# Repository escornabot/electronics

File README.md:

## Catalog
- [Escorna CPU][CPU01] is 50x50mm to 50x100mm board to use with Arduino Nano. It integrates keypad on board on 2x

- [Escorna_CPU_2_4][CPU240] It is a pcb that integrates an ATmega328P, a step-up (to use 1.2V batteries) and the rest of the electronics needed to build an Escornabot.

- [Arduino Shield][ARD01] is an Arduino Uno compatible
  shield ready to use with the Escornabot's motors and also integrates a keypad.

- [Cervus][CER01] is a board based on powerful ATmega32u4
  microcontroler and compatible with Arduino shields.
- [E_Keypad][KEY01] Is a 50x50mm board with 6  and 5 buttons and
  connects to any Escornabot.

- [E_KEY_BT][E_KEY_BT] Escornabot keyboard with MakeyMakey type sensors on the E_KEY_BT board.
   Any object that is minimally conductive can be used. Adjusting the value
   threshold: higher for less sensitivity, nothing needs to be changed in the
   robot firmware.

- [E_KEY_FICHA][E_KEY_FICHA] It allows the programming of Escornabot using printed or cut-out cards (cardboard ..) communicating the commands via Bluetooth.
  using @arduino Nano, easy to print, manageable and expandable to 15 "Tabs" thanks to the firmware of @caligari_pub

- [escoRnaFID][RnaFID]PCB for the project for children with visual impairment or blindness,
  developed by Angel Villanueva [@avilmaru][@avil] to control an Escornabot with RFID cards

## License

Every content in this repo, otherwise specified under subdirectories, is
licensed under [Creative Commons BY-SA][LICENSEcc] or [CERN Open Hardware Licence -W- V2][OHL-W-V2].
(by [XDeSIG][XDE01])

## To buy boards

Developer don't produce boards to sell. Under [_provider_][provider]
directory there are instructions to order yourself.

Are you a board provider? Please, send us your buyer's guide! :-)

[CPU01]: EscornaCPU
[CPU240]: https://github.com/xdesig/escornabot-electronics/tree/master/Electronics/EscornaCPU/2.x/2.40
[ARD01]: ArduinoShield
[CER01]: Cervus
[KEY01]: E_KEYPAD
[RnaFID]: escoRnaFID
[E_KEY_BT]: E_KEY_BT
[@avil]: https://twitter.com/avilmaru
[XDE01]: https://twitter.com/xdesig
[provider]: https://www.pcbway.com/project/member/?bmbno=6FE4DE76-9D11-4C
[LICENSEcc]: https://creativecommons.org/licenses/by-sa/3.0/es
[OHL-W-V2]: https://ohwr.org/project/cernohl/wikis/Documents/CERN-OHL-version-2

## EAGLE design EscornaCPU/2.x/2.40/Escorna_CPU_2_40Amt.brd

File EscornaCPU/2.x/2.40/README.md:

## Escorna CPU 2.4
This PCB integrates an ATmega328P, a step-up (great to use with 1.2V batteries, suggestion made by [caligari](https://github.com/rafacouto)) and the rest of the electronics needed to build a full-compatible Escornabot.
USB communications are supported by CH340E<br>
Arduino Uno, Arduino Nano compatible or ATmega minicore

## License

<br><br><br><br>

## Open Hardware Certification program

<br><br><br><br><br><br><br>

## To buy boards
Developer doesn't produce boards to get money. [_provider_][provider]

Are you a board provider? Please, send us your buyer's guide! xdesig@gmail.com

[XDE01]: https://twitter.com/xdesig
[provider]: https://www.pcbway.com/project/shareproject/Escorna_CPU_2_4.html
[LICENSEcc]: https://creativecommons.org/licenses/by-sa/3.0/es
[OHL-W-V2]: https://ohwr.org/project/cernohl/wikis/Documents/CERN-OHL-version-2

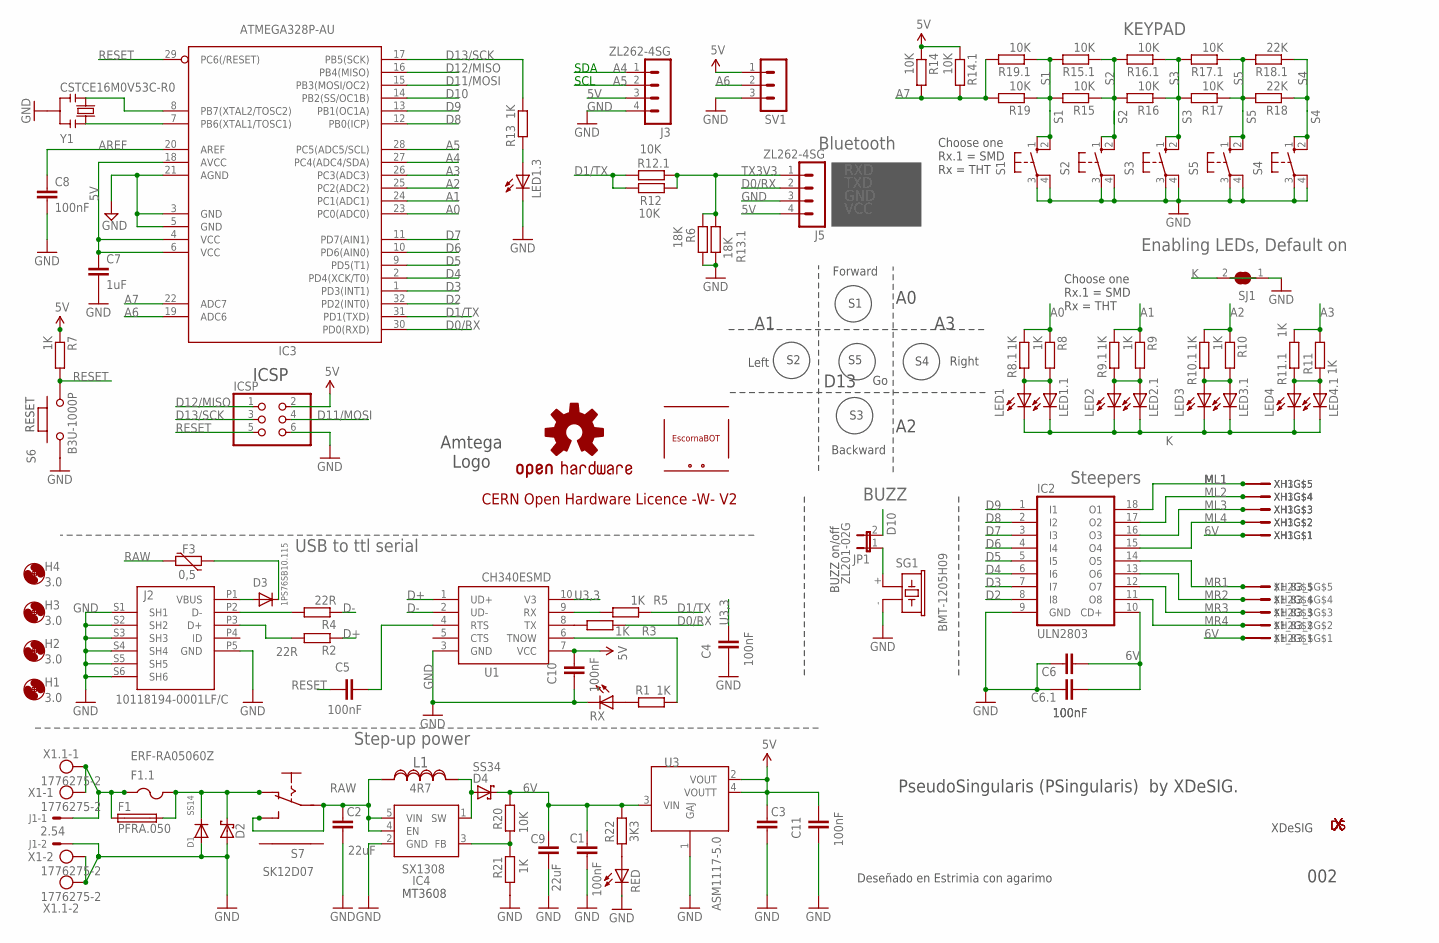
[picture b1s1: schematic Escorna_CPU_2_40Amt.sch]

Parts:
$1_82_$: XDESIG_XDESIG21; XDESIG_XDESIG
$1_83_$: B5B-XH-A
C1, C4, C5, C8, C10, C11: 100nF; C0603-ROUND
C2, C9: 22uF; C1206K
C3: 10uF; C1206K
C6: 100nF; C025-024X044
C6.1: 100nF; C0603K
C7: 1uF; C0603-ROUND
D1: SS14; SMADIODE
D2: 1N5817; DO41-10
D3: 1PS76SB10.115; SOD-323F
D4: SS34; DIODE_SMA
ESC: ESCORNABOT; ESCORNA_PEQUE
F1: PFRA.050; TE5
F1.1: ERF-RA05060Z; R1206
F3: 0,5; R1206
H1, H2, H3, H4: 3.0; 3,0
IC2: ULN2803; DIL18
IC3: ATMEGA328P-AU; TQFP32-08
IC4: SX1308; SOT23-6
ICSP: 0114_PH254-203DF118A00V; 2X03
J1: 2.54; 6410-02
J2: 10118194-0001LF/C; SMARTPRJ_CON2_USB_MICRO_B_AT
J3, J5: ZL262-4SG; MA04-1
JP1: ZL201-02G; JP1
L1: 4R7; SRN6045
LED1, LED2, LED3, LED4: LED3MM
LED1.1, LED1.3, LED2.1, LED3.1, LED4.1: LEDCHIPLED_0603; CHIPLED_0603
LOGO2: OSHW-LOGOL; ESCORNA_LBRESCORNA_CPU_2_10_SPARKFUN-AESTHETICS_OSHW-LOGO-L
R1, R3, R5, R7, R8.1, R9.1, R10.1, R11.1, R13, R21: 1K; R0603
R2, R4: 22R; R0603
R6: 18K; 0204/7
R8, R9, R10, R11: 1K; 0204/7
R12, R14, R15, R16, R17, R19: 10K; 0204/7
R12.1, R14.1, R15.1, R16.1, R17.1, R19.1, R20: 10K; R0603
R13.1: 18K; R0603
R18: 22K; 0204/7
R18.1: 22K; R0603
R22: 3K3; R0603
RED: LEDCHIPLED_0603; CHIPLED_0603
RX: LEDCHIPLED_0603; CHIPLED_0603
S1, S2, S3, S4, S5: 40-XX; B3F-40
S6: B3U-1000P; SMD_157SW
S7: SK12D07; ESCORNA_SK-12D07
SG1: BMT-1205H09; F/CM12P
SJ1: SJ
SV1: MA03-1
U1: CH340ESMD; MSOP10
U3: ASM1117-5.0; SOT223
X1, X1.1: 1776275-2; AK550/2
XDS2: XDESIG; XDESIG_CU_2
XH1, XH2, XH3: B5B-XH-A
Y1: CSTCE16M0V53C-R0; RESONATOR

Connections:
5V: C3.2, C7.1, C10.2, C11.2, IC3.4 (VCC), IC3.6 (VCC), IC3.18 (AVCC), ICSP.2, J3.3, J5.4, R7.1, R14.1, R14.1.1, SV1.1, U1.7 (VCC), U3.2 (VOUT), U3.4 (VOUTT)
6V: $1_83_$.P$1, C1.2, C6.2, C6.1.2, C9.2, D4.C, IC2.10 (CD+), R20.1, R22.1, U3.3 (VIN), XH1.P$1, XH2.P$1, XH3.P$1
+D: J2.P3 (D+), R2.2
-D: J2.P2 (D-), R4.2
A0: IC3.23 (PC0(ADC0)), R8.1, R8.1.1
A1: IC3.24 (PC1(ADC1)), R9.1, R9.1.1
A2: IC3.25 (PC2(ADC2)), R10.1, R10.1.1
A3: IC3.26 (PC3(ADC3)), R11.2, R11.1.1
A4: IC3.27 (PC4(ADC4/SDA)), J3.1
A5: IC3.28 (PC5(ADC5/SCL)), J3.2
A6: IC3.19 (ADC6), SV1.2
A7: IC3.22 (ADC7), R14.2, R14.1.2, R19.2, R19.1.2
AREF: C8.1, IC3.20 (AREF)
D0/RX: IC3.30 (PD0(RXD)), J5.2, R3.1
D1/TX: IC3.31 (PD1(TXD)), R5.1, R12.1, R12.1.1
D2: IC2.8 (I8), IC3.32 (PD2(INT0))
D3: IC2.7 (I7), IC3.1 (PD3(INT1))
D4: IC2.6 (I6), IC3.2 (PD4(XCK/T0))
D5: IC2.5 (I5), IC3.9 (PD5(T1))
D6: IC2.4 (I4), IC3.10 (PD6(AIN0))
D7: IC2.3 (I3), IC3.11 (PD7(AIN1))
D8: IC2.2 (I2), IC3.12 (PB0(ICP))
D9: IC2.1 (I1), IC3.13 (PB1(OC1A))
D10: IC3.14 (PB2(SS/OC1B)), JP1.2
D11/MOSI: IC3.15 (PB3(MOSI/OC2)), ICSP.4
D12/MISO: IC3.16 (PB4(MISO)), ICSP.1
D13/SCK: IC3.17 (PB5(SCK)), ICSP.3, R13.1
D+: R2.1, U1.1 (UD+)
D-: R4.1, U1.2 (UD-)
DTR?: C5.2, U1.4 (RTS)
GND: C1.1, C2.1, C3.1, C4.1, C6.1, C6.1.1, C7.2, C8.2, C9.1, C10.1, C11.1, D1.A, D2.A, IC2.9 (GND), IC3.3 (GND), IC3.5 (GND), IC3.21 (AGND), IC4.2 (GND), ICSP.6, J1.2, J2.P5 (GND), J2.S1 (SH1), J2.S2 (SH2), J2.S3 (SH3), J2.S4 (SH4), J2.S5 (SH5), J2.S6 (SH6), J3.4, J5.3, LED1.3.C, R6.2, R13.1.1, R21.2, RED.C, RX.C, S1.3, S1.4 (P1), S2.3, S2.4 (P1), S3.3, S3.4 (P1), S4.3, S4.4 (P1), S5.3, S5.4 (P1), S6.1, SG1.- (2), SJ1.1, SV1.3, U1.3 (GND), U3.1 (GAJ), X1.2, X1.1.2, Y1.2
K: LED1.K (C), LED1.1.C, LED2.K (C), LED2.1.C, LED3.K (C), LED3.1.C, LED4.K (C), LED4.1.C, SJ1.2
ML1: IC2.18 (O1), XH1.P$5, XH3.P$5
ML2: IC2.17 (O2), XH1.P$4, XH3.P$4
ML3: IC2.16 (O3), XH1.P$3, XH3.P$3
ML4: IC2.15 (O4), XH1.P$2, XH3.P$2
MR1: $1_83_$.P$5, IC2.14 (O5), XH2.P$5
MR2: $1_83_$.P$4, IC2.13 (O6), XH2.P$4
MR3: $1_83_$.P$3, IC2.12 (O7), XH2.P$3
MR4: $1_83_$.P$2, IC2.11 (O8), XH2.P$2
unnamed: JP1.1, SG1.+ (1)
unnamed: D1.C, D2.C, F1.2, F1.1.2, S7.P$2 (O)
unnamed: LED2.A, LED2.1.A, R9.2, R9.1.2
unnamed: LED1.A, LED1.1.A, R8.2, R8.1.2
unnamed: LED3.A, LED3.1.A, R10.2, R10.1.2
unnamed: LED4.A, LED4.1.A, R11.1, R11.1.2
unnamed: D3.A, J2.P1 (VBUS)
unnamed: F1.1, F1.1.1, J1.1, X1.1, X1.1.1
unnamed: R1.2, RX.A
unnamed: IC4.3 (FB), R20.2, R21.1
unnamed: IC3.7 (PB6(XTAL1/TOSC1)), Y1.1
unnamed: IC3.8 (PB7(XTAL2/TOSC2)), Y1.3
unnamed: LED1.3.A, R13.2
unnamed: D4.A, IC4.1 (SW), L1.1
unnamed: D3.C, F3.1
unnamed: R22.2, RED.A
unnamed: R5.2, U1.9 (RX)
unnamed: R3.2, U1.8 (TX)
unnamed: R1.1, U1.6 (TNOW)
RAW: C2.2, F3.2, IC4.4 (EN), IC4.5 (VIN), L1.2, S7.P$1, S7.P$3 (S)
RESET: C5.1, IC3.29 (PC6(/RESET)), ICSP.5, R7.2, S6.2
S1: R15.2, R15.1.2, R19.1, R19.1.1, S1.1 (S), S1.2 (S1)
S2: R15.1, R15.1.1, R16.2, R16.1.2, S2.1 (S), S2.2 (S1)
S3: R16.1, R16.1.1, R17.2, R17.1.2, S3.1 (S), S3.2 (S1)
S4: R18.1, R18.1.1, S4.1 (S), S4.2 (S1)
S5: R17.1, R17.1.1, R18.2, R18.1.2, S5.1 (S), S5.2 (S1)
TX3V3: J5.1, R6.1, R12.2, R12.1.2, R13.1.2
U3,3: C4.2, U1.10 (V3)

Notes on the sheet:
Steepers
KEYPAD
BUZZ
CERN Open Hardware Licence -W- V2
Forward
Left
Right
Backward
Choose one Rx.1 = SMD Rx = THT
XDeSIG
PseudoSingularis (PSingularis) by XDeSIG.
002
Enabling LEDs, Default on
BUZZ on/off
D13
SCL
SDA
ICSP
Bluetooth
RXD
TXD
GND
VCC
RESET
Deseñado en Estrimia con agarimo
SX1308
IC4
USB to ttl serial
Step-up power
MT3608
Amtega Logo

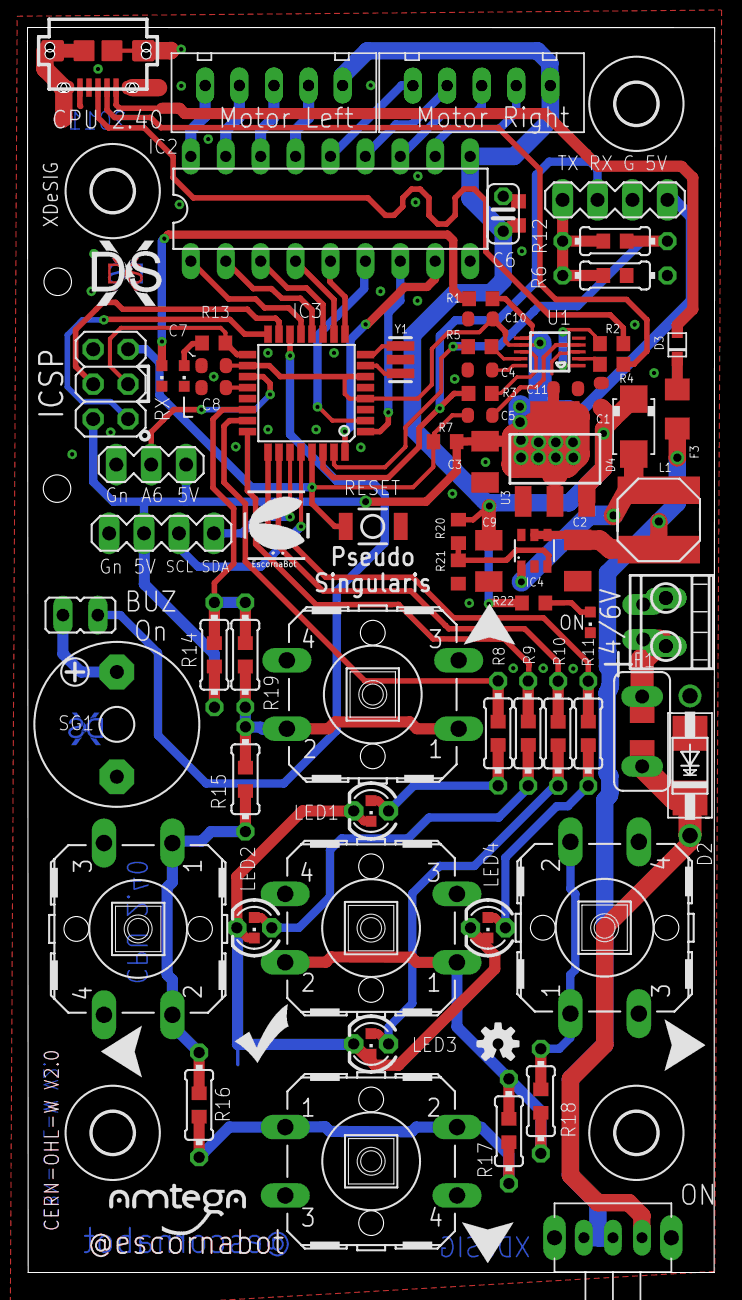
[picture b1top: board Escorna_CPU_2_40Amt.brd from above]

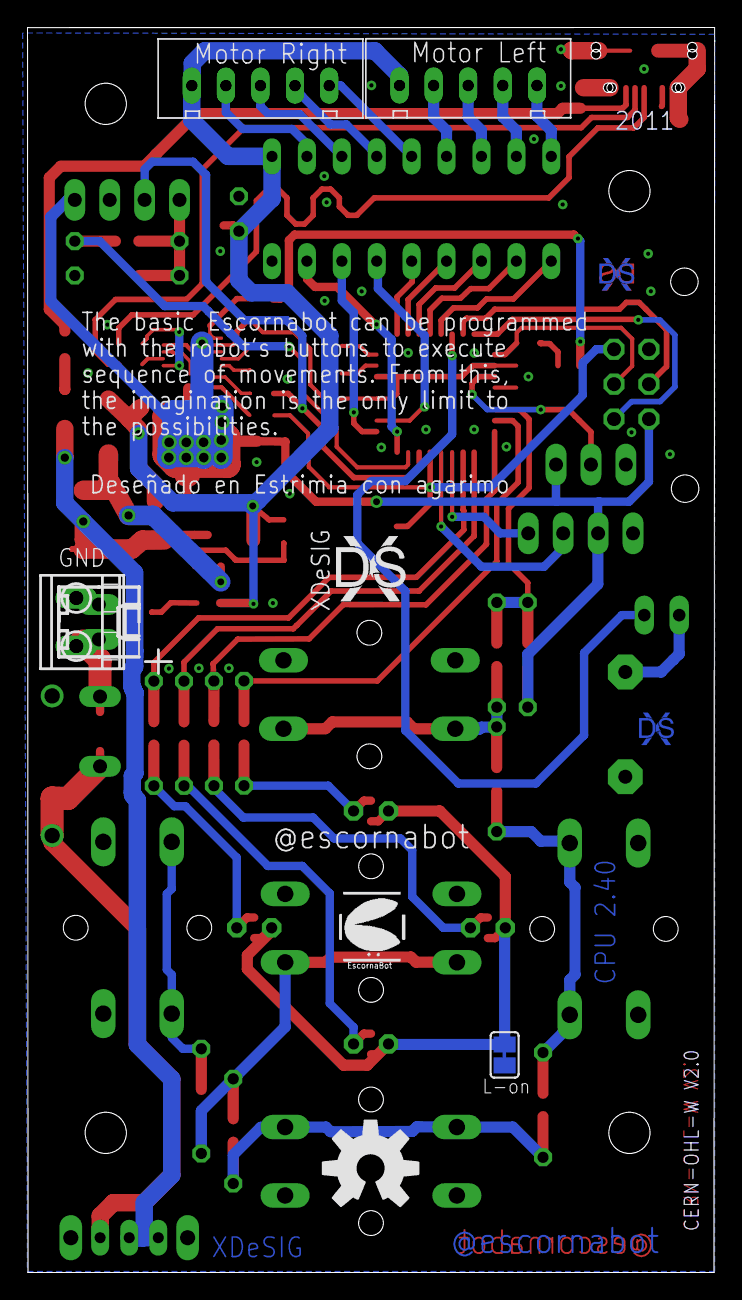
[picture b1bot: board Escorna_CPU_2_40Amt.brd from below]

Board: 2 copper layers, 50.0 x 90.6 mm, 112 parts (10 on the bottom side), 68 nets.

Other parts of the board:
LOGO1: OSHW-LOGOS; OSHW-LOGO-S
U$1: AMTEGA
U$4, U$7, U$8, U$9: FRECHA
U$5: ESCORNABOT; ESCORNA_PEQUE
U$10: GO; VALE
U$12: XDESIG_XDESIG21; XDESIG_XDESIG
XDS, XDS1: XDESIG; XDESIG_CU_2

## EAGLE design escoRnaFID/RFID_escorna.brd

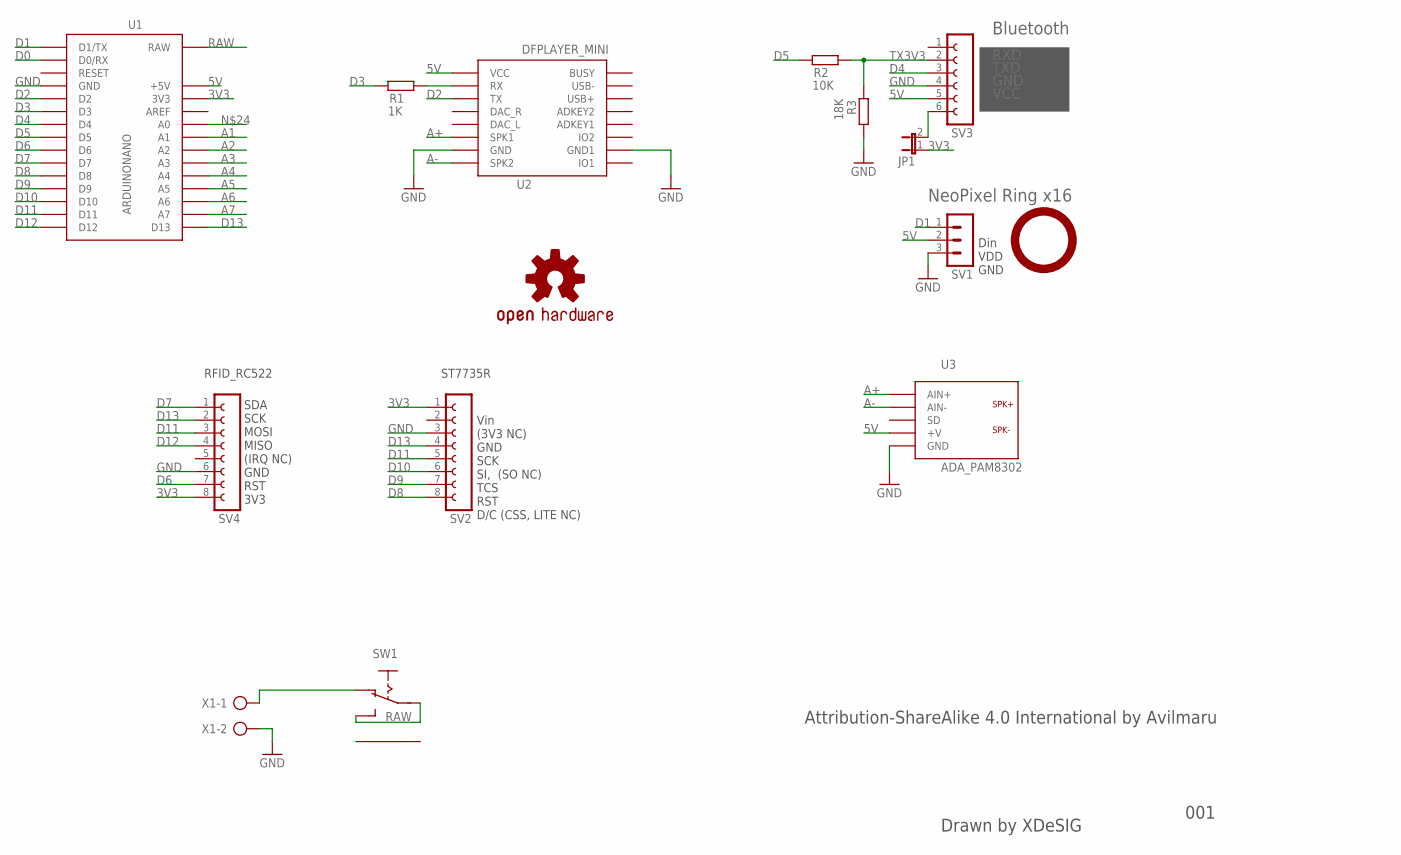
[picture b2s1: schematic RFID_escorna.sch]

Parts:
JP1: JUMPER_JP1E; JUMPER_JP1
LOGO1: OSHW-LOGOS; ESCORNA_LBRESCORNA_CPU_2_10_SPARKFUN-AESTHETICS_OSHW-LOGO-S
R1: 1K; 0204/7
R2: 10K; 0204/7
R3: 18K; 0204/7
SV1: MA03-1
SV2, SV4: FE08-1; FE08
SV3: FE06-1; FE06
SW1: ESCORNA_ELIB_ESCORNA_SK12F14D; ESCORNA_ELIB_ESCORNA_SK-12D07
U1: ARDUINONANO; ARDUINO_NANO_NO_ICSP
U2: DFPLAYER_MINI; DFR0299
U3: ADA_PAM8302; ADA_PAM8320
X1: AK500/2

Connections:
3V3: JP1.1, SV2.1, SV4.8, U1.3V3
5V: SV1.2, SV3.5, U1.5V (+5V), U2.P$1 (VCC), U3.P$2 (+V)
A1: U1.A1
A2: U1.A2
A3: U1.A3
A4: U1.A4
A5: U1.A5
A6: U1.A6
A7: U1.A7
A+: U2.P$6 (SPK1), U3.P$5 (AIN+)
A-: U2.P$8 (SPK2), U3.P$4 (AIN-)
D0: U1.D0/RX
D1: SV1.1, U1.D1/TX
D2: U1.D2, U2.P$3 (TX)
D3: R1.1, U1.D3
D4: SV3.3, U1.D4
D5: R2.1, U1.D5
D6: SV4.7, U1.D6
D7: SV4.1, U1.D7
D8: SV2.8, U1.D8
D9: SV2.7, U1.D9
D10: SV2.6, U1.D10
D11: SV2.5, SV4.3, U1.D11
D12: SV4.4, U1.D12
D13: SV2.4, SV4.2, U1.D13
GND: R3.2, SV1.3, SV2.3, SV3.4, SV4.6, U1.GND, U1.GND1 (GND), U2.P$7 (GND), U2.P$10 (GND1), U3.P$1 (GND), X1.2
unnamed: JP1.2, SV3.6
unnamed: SW1.P$2 (O), X1.1
unnamed: R1.2, U2.P$2 (RX)
RAW: SW1.P$1, SW1.P$3 (S), U1.RAW
TX3V3: R2.2, R3.1, SV3.2

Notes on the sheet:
Bluetooth
RXD
TXD
GND
VCC
NeoPixel Ring x16
RFID_RC522
SDA SCK MOSI MISO (IRQ NC) GND RST 3V3
ST7735R
Vin (3V3 NC) GND SCK SI, (SO NC) TCS RST D/C (CSS, LITE NC)
001
Din VDD GND
Attribution-ShareAlike 4.0 International by Avilmaru
Drawn by XDeSIG

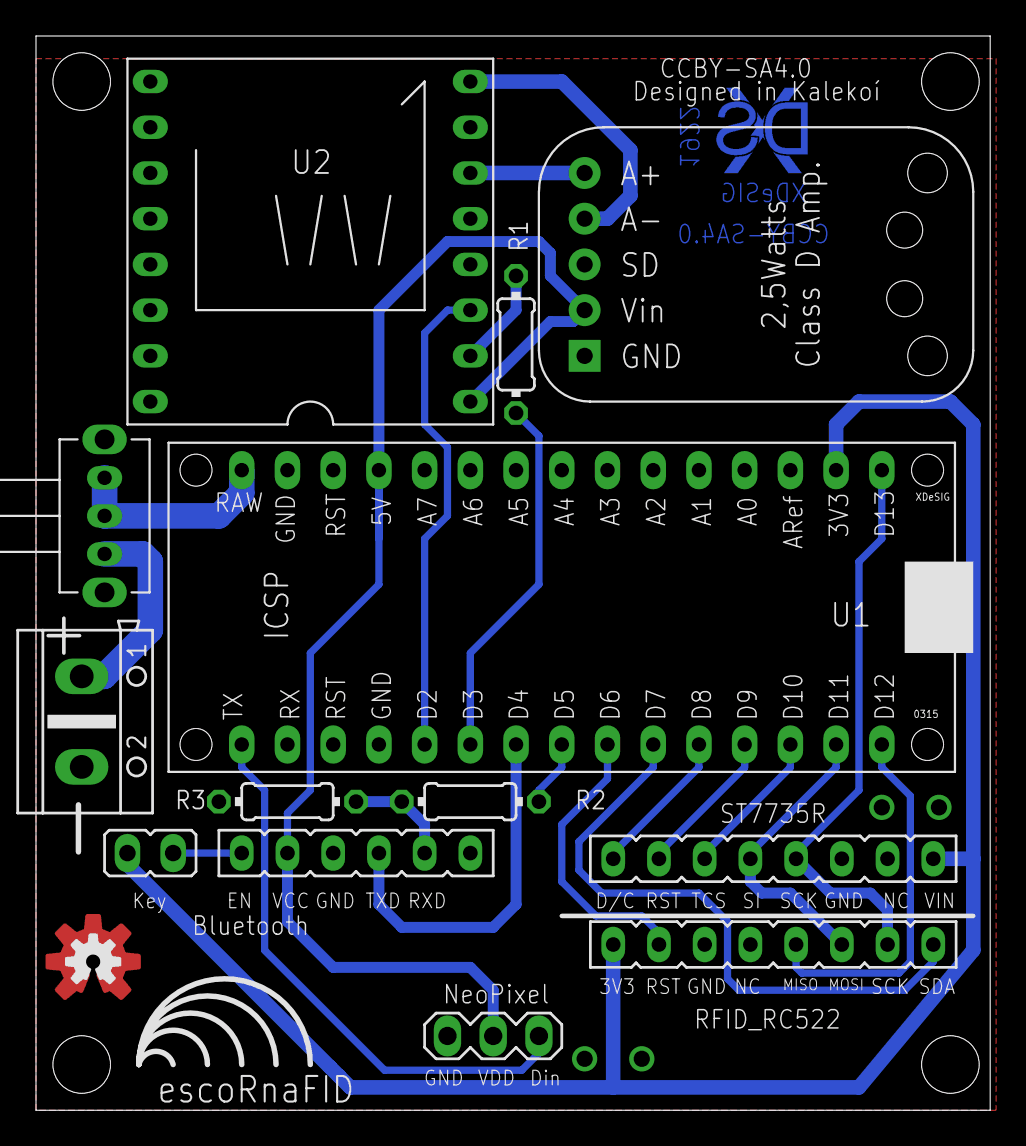
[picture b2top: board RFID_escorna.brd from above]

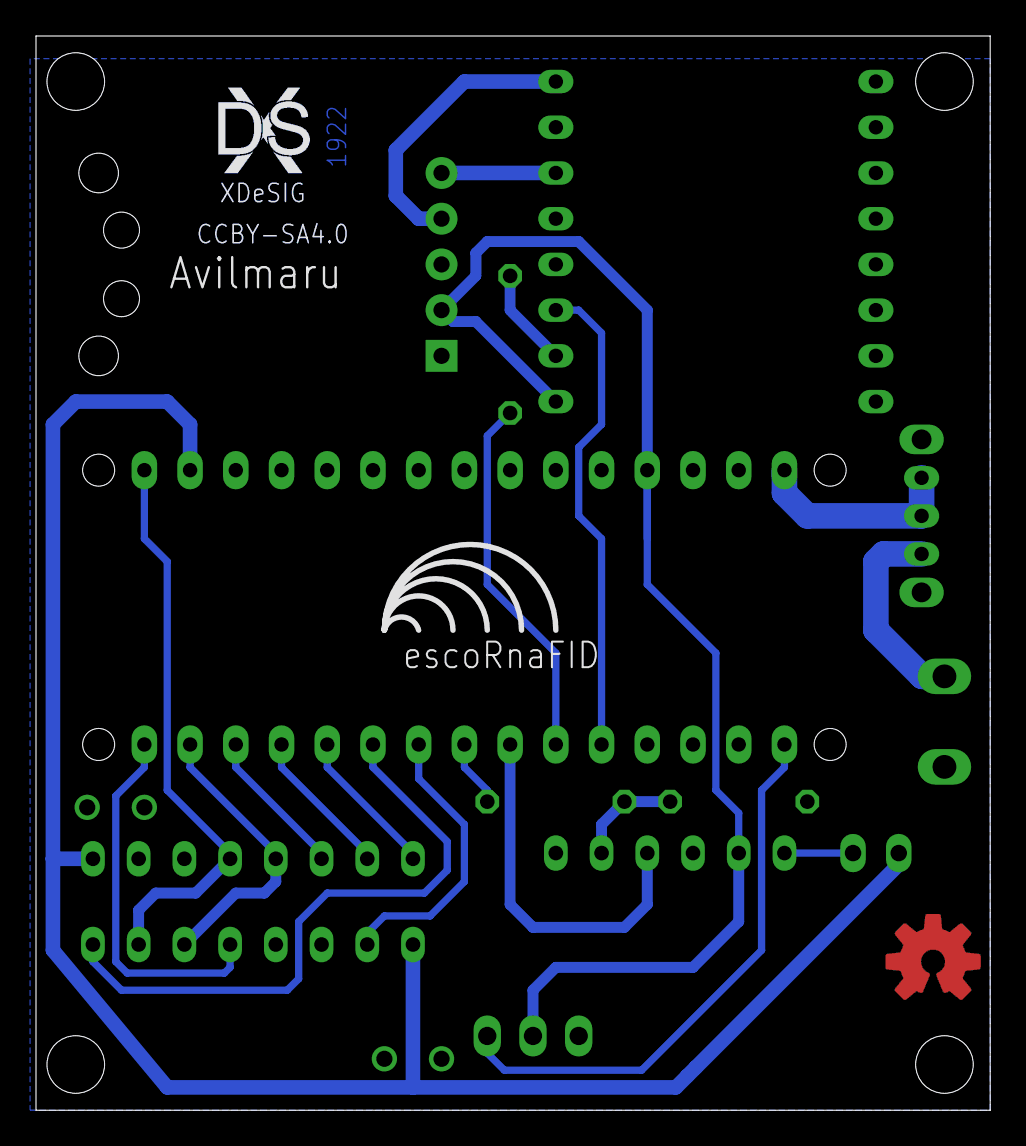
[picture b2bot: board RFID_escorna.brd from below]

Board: 2 copper layers, 53.0 x 59.7 mm, 17 parts (2 on the bottom side), 23 nets.

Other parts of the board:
U$1: XDESIG_CU
U$2: OSHWLOGO_TOP_0.2
U$5: XDESIG

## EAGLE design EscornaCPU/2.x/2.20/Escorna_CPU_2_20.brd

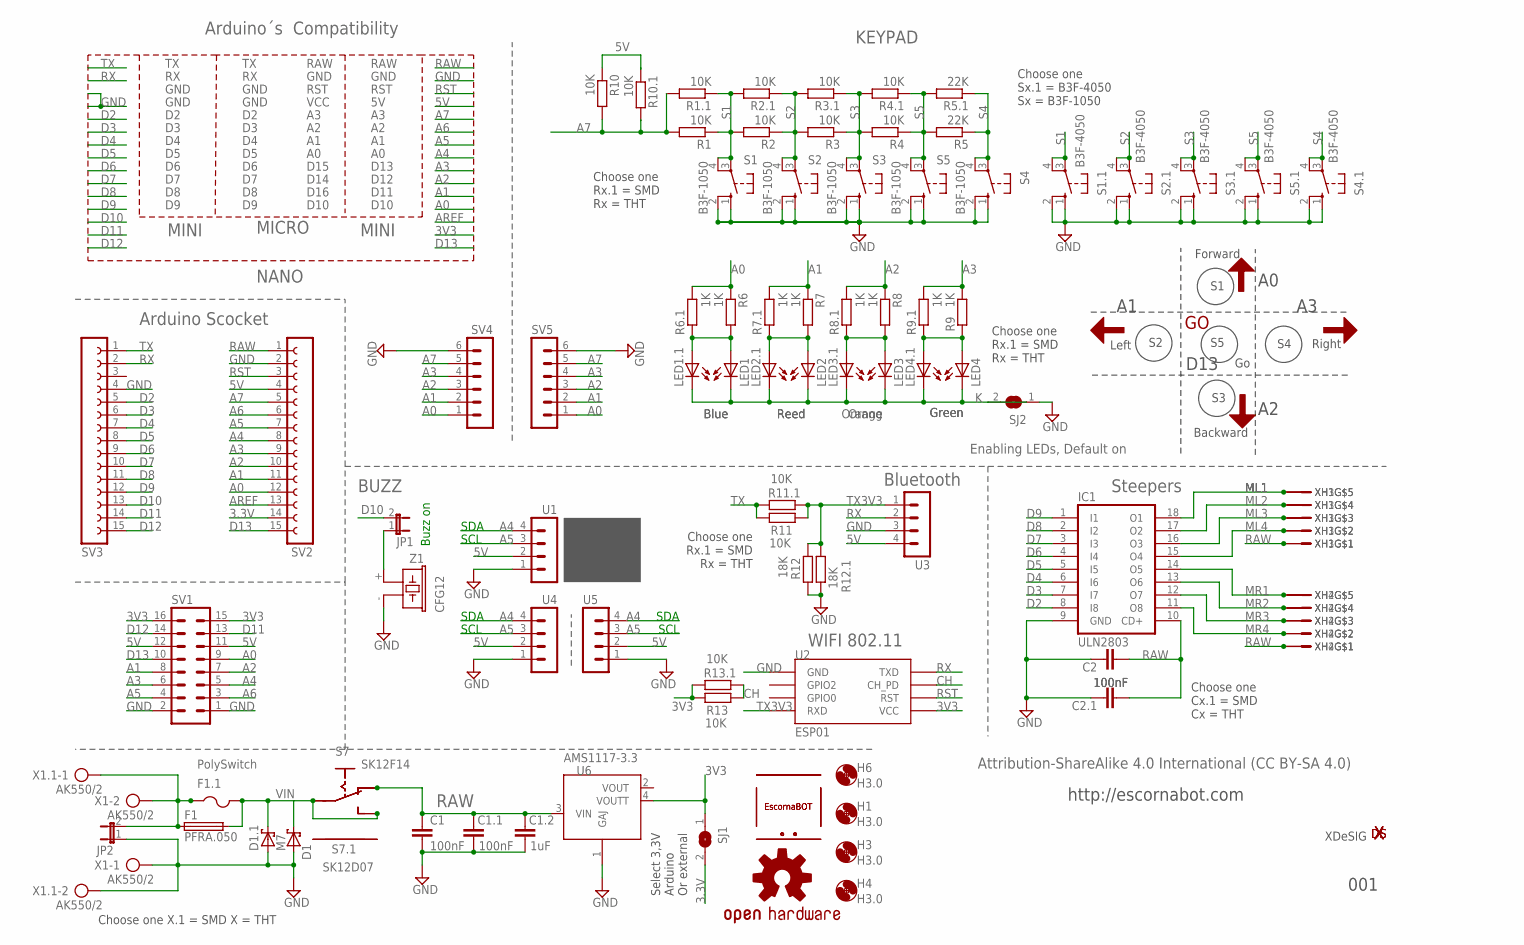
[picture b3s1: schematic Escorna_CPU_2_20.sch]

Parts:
C1, C2: 100nF; C025-025X050
C1.1, C2.1: 100nF; C0603K
C1.2: 1uF; C0603K
D1: 1N5817; DO41-10
D1.1: M7; SMA
ESC1, ESC2: ESCORNABOT; ESCORNA_PEQUE
F1: PFRA.050; TE5
F1.1: PolySwitch; R1206
H1, H3, H4, H6: H3.0; 3,0
IC1: ULN2803; DIL18
JP1, JP2: JP1E; 1X02
LED1: Blue; LED3MM
LED1.1: Blue; CHIPLED_0603
LED2: Reed; LED3MM
LED2.1: Reed; CHIPLED_0603
LED3: Orange; LED3MM
LED3.1: Orang; CHIPLED_0603
LED4: Green; LED3MM
LED4.1: Green; CHIPLED_0603
LOGO2: OSHW-LOGOS; OSHW-LOGO-S
R1, R2, R3, R4, R10, R11, R13: 10K; 0204/7
R1.1, R2.1, R3.1, R4.1, R10.1, R11.1, R13.1: 10K; R0603
R5: 22K; 0204/7
R5.1: 22K; R0603
R6, R7, R8, R9: 1K; 0204/7
R6.1, R7.1, R8.1, R9.1: 1K; R0603
R12: 18K; 0204/7
R12.1: 18K; R0603
S1, S2, S3, S4, S5: B3F-1050; B3F-10XX
S1.1, S2.1, S3.1, S4.1, S5.1: B3F-4050; B3F-40XX
S7: SK12F14; ESCORNA_SK-12F14-G
S7.1: SK12D07; ESCORNA_SK-12D07
SJ1, SJ2: SJ
SV1: MA08-2
SV2, SV3: 1x15 SOCKET STRIP; CON-LSTA_FE15
SV4, SV5: MA06-1
U1, U3, U4, U5: MA04-1
U2: ESP01
U6: AMS1117-3.3; SOT223
U$1, U$3, U$6, U$11: FRECHA
U$2: GO; VALE
U$13: XDESIG_XDESIG21; XDESIG_XDESIG
X1, X1.1: AK550/2
XDS1: XDESIG; XDESIG_CU_2
XH1, XH2, XH3, XH4: B5B-XH-A
Z1: CFG12; F/CM12P

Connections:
3.3V: SJ1.2, SV2.14
3V3: R13.1, R13.1.1, SJ1.1, SV1.15, SV1.16, U2.VCC, U6.4 (VOUTT)
5V: R10.1, R10.1.1, SV1.11, SV1.12, SV2.4, U1.2, U3.4, U4.2, U5.2
A0: R6.1, R6.1.1, SV1.9, SV2.12, SV4.1, SV5.1
A1: R7.1, R7.1.1, SV1.8, SV2.11, SV4.2, SV5.2
A2: R8.1, R8.1.1, SV1.7, SV2.10, SV4.3, SV5.3
A3: R9.2, R9.1.1, SV1.6, SV2.9, SV4.4, SV5.4
A4: SV1.5, SV2.8, U1.4, U4.4, U5.4
A5: SV1.4, SV2.7, U1.3, U4.3, U5.3
A6: SV1.3, SV2.6
A7: R1.2, R1.1.2, R10.2, R10.1.2, SV2.5, SV4.5, SV5.5
AREF: SV2.13
CH: R13.2, R13.1.2, U2.CH_PD
D2: IC1.8 (I8), SV3.5
D3: IC1.7 (I7), SV3.6
D4: IC1.6 (I6), SV3.7
D5: IC1.5 (I5), SV3.8
D6: IC1.4 (I4), SV3.9
D7: IC1.3 (I3), SV3.10
D8: IC1.2 (I2), SV3.11
D9: IC1.1 (I1), SV3.12
D10: JP1.2, SV3.13
D11: SV1.13, SV3.14
D12: SV1.14, SV3.15
D13: SV1.10, SV2.15
GND: C1.2, C1.1.1, C1.2.1, C2.1, C2.1.1, D1.A, D1.1.A, IC1.9 (GND), JP2.1, R12.2, R12.1.1, S1.1 (S), S1.2 (S1), S1.1.1 (S), S1.1.2 (S1), S2.1 (S), S2.2 (S1), S2.1.1 (S), S2.1.2 (S1), S3.1 (S), S3.2 (S1), S3.1.1 (S), S3.1.2 (S1), S4.1 (S), S4.2 (S1), S4.1.1 (S), S4.1.2 (S1), S5.1 (S), S5.2 (S1), S5.1.1 (S), S5.1.2 (S1), SJ2.1, SV1.1, SV1.2, SV2.2, SV3.4, SV4.6, SV5.6, U1.1, U2.GND, U3.3, U4.1, U5.1, U6.1 (GAJ), X1.1, X1.1.2, Z1.- (2)
K: LED1.K (C), LED1.1.C, LED2.K (C), LED2.1.C, LED3.K (C), LED3.1.C, LED4.K (C), LED4.1.C, SJ2.2
ML1: IC1.18 (O1), XH1.P$5, XH3.P$5
ML2: IC1.17 (O2), XH1.P$4, XH3.P$4
ML3: IC1.16 (O3), XH1.P$3, XH3.P$3
ML4: IC1.15 (O4), XH1.P$2, XH3.P$2
MR1: IC1.14 (O5), XH2.P$5, XH4.P$5
MR2: IC1.13 (O6), XH2.P$4, XH4.P$4
MR3: IC1.12 (O7), XH2.P$3, XH4.P$3
MR4: IC1.11 (O8), XH2.P$2, XH4.P$2
unnamed: JP1.1, Z1.+ (1)
unnamed: F1.1, F1.1.1, JP2.2, X1.2, X1.1.1
unnamed: LED2.A, LED2.1.A, R7.2, R7.1.2
unnamed: LED1.A, LED1.1.A, R6.2, R6.1.2
unnamed: LED3.A, LED3.1.A, R8.2, R8.1.2
unnamed: LED4.A, LED4.1.A, R9.1, R9.1.2
unnamed: S7.P$4, S7.1.P$4
unnamed: S7.P$5, S7.1.P$5
RAW: C1.1, C1.1.2, C1.2.2, C2.2, C2.1.2, IC1.10 (CD+), S7.P$2 (O), S7.1.P$2 (O), SV2.1, U6.3 (VIN), XH1.P$1, XH2.P$1, XH3.P$1, XH4.P$1
RST: SV2.3, U2.RST
RX: SV3.2, U2.TX (TXD), U3.2
S1: R1.1, R1.1.1, R2.2, R2.1.2, S1.3, S1.4 (P1), S1.1.3, S1.1.4 (P1)
S2: R2.1, R2.1.1, R3.2, R3.1.2, S2.3, S2.4 (P1), S2.1.3, S2.1.4 (P1)
S3: R3.1, R3.1.1, R4.2, R4.1.2, S3.3, S3.4 (P1), S3.1.3, S3.1.4 (P1)
S4: R5.1, R5.1.1, S4.3, S4.4 (P1), S4.1.3, S4.1.4 (P1)
S5: R4.1, R4.1.1, R5.2, R5.1.2, S5.3, S5.4 (P1), S5.1.3, S5.1.4 (P1)
TX: R11.1, R11.1.1, SV3.1
TX3V3: R11.2, R11.1.2, R12.1, R12.1.2, U2.RX (RXD), U3.1
VIN: D1.C, D1.1.C, F1.2, F1.1.2, S7.P$1, S7.P$3 (S), S7.1.P$1, S7.1.P$3 (S)

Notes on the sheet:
Arduino Scocket
Steepers
KEYPAD
BUZZ
Bluetooth
Buzz on
NANO
Arduino´s Compatibility
MINI
MICRO
GND
RAW
RST
VCC
D13
D15
D12
D14
D11
D16
D10
Attribution-ShareAlike 4.0 International (CC BY-SA 4.0)
Forward
Left
Right
Backward
WIFI 802.11
Choose one Rx.1 = SMD Rx = THT
Choose one X.1 = SMD X = THT
XDeSIG
http://escornabot.com
Choose one Cx.1 = SMD Cx = THT
001
Enabling LEDs, Default on
SCL
SDA
Choose one Sx.1 = B3F-4050 Sx = B3F-1050
Select 3,3V Arduino Or external

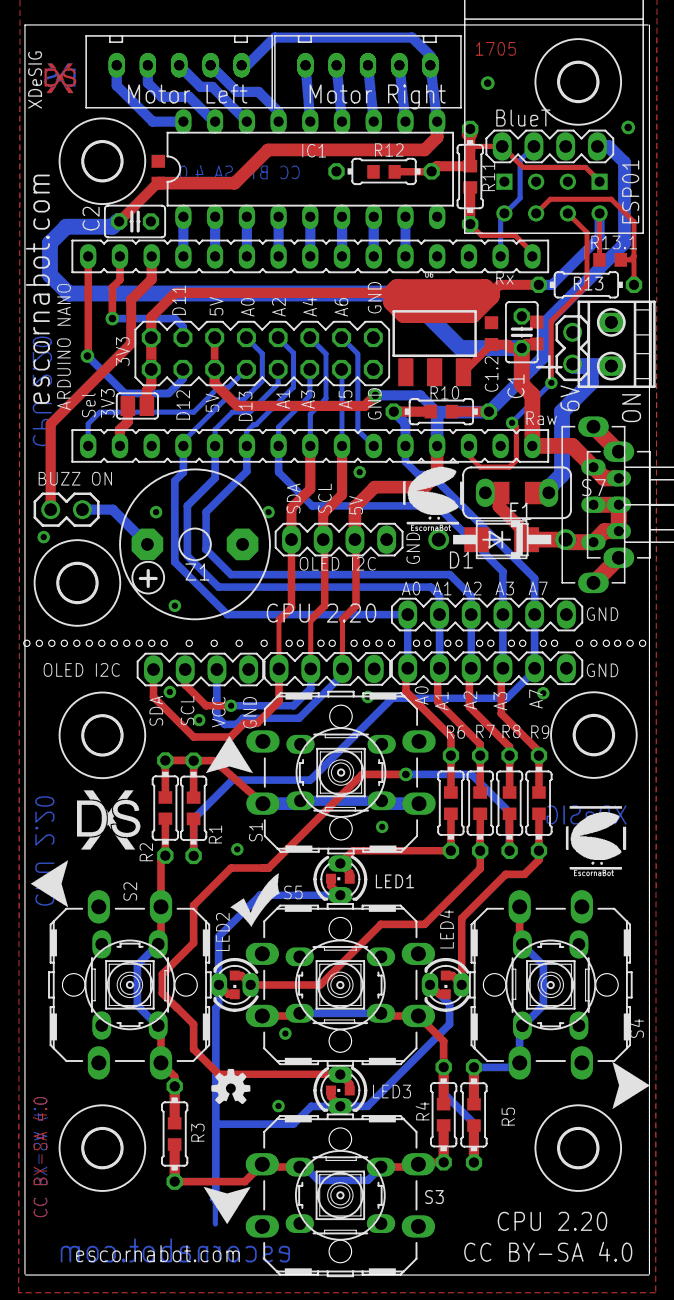
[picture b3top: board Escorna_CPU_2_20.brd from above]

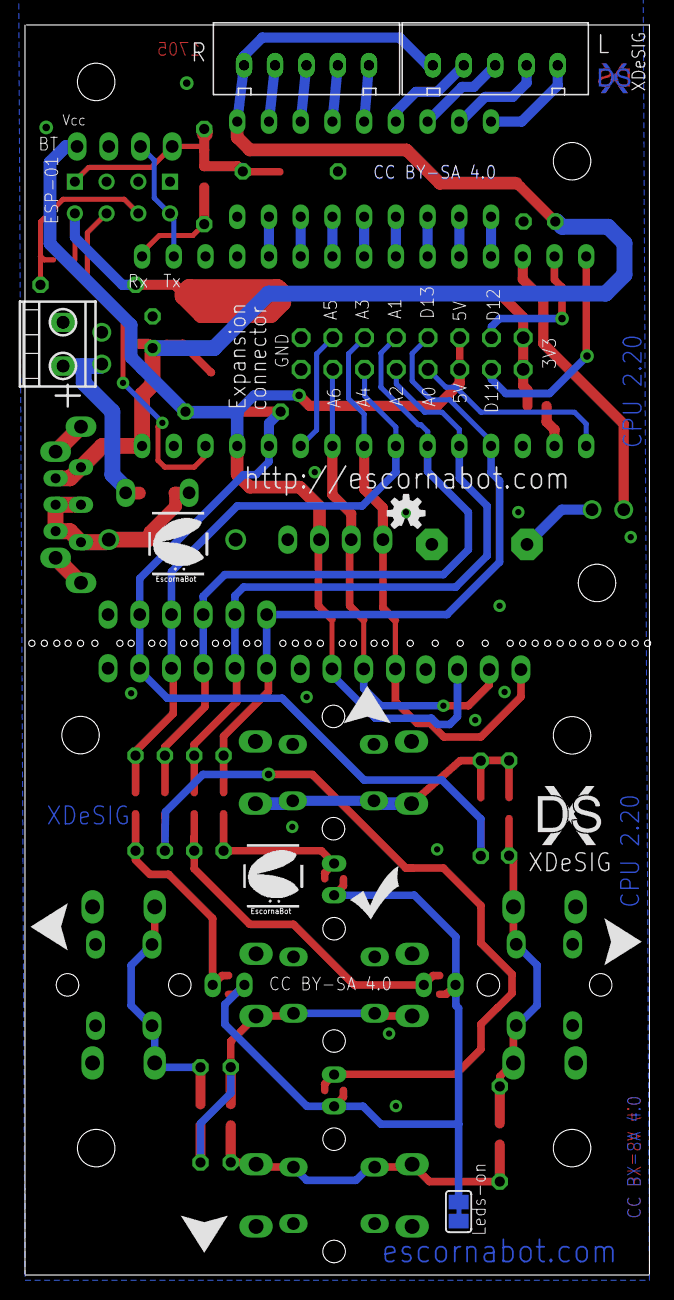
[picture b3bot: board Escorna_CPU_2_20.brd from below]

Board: 2 copper layers, 50.0 x 100.1 mm, 105 parts (14 on the bottom side), 53 nets.

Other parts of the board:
ESC: ESCORNABOT; ESCORNA_PEQUE
H2, H5, H7: MOUNT-HOLE3.0; 3,0
LOGO1: OSHW-LOGOS; OSHW-LOGO-S
U$4, U$7, U$8, U$9: FRECHA
U$5: ESCORNABOT; ESCORNA_PEQUE
U$10: GO; VALE
U$12: XDESIG_XDESIG21; XDESIG_XDESIG
XDS: XDESIG; XDESIG_CU_2

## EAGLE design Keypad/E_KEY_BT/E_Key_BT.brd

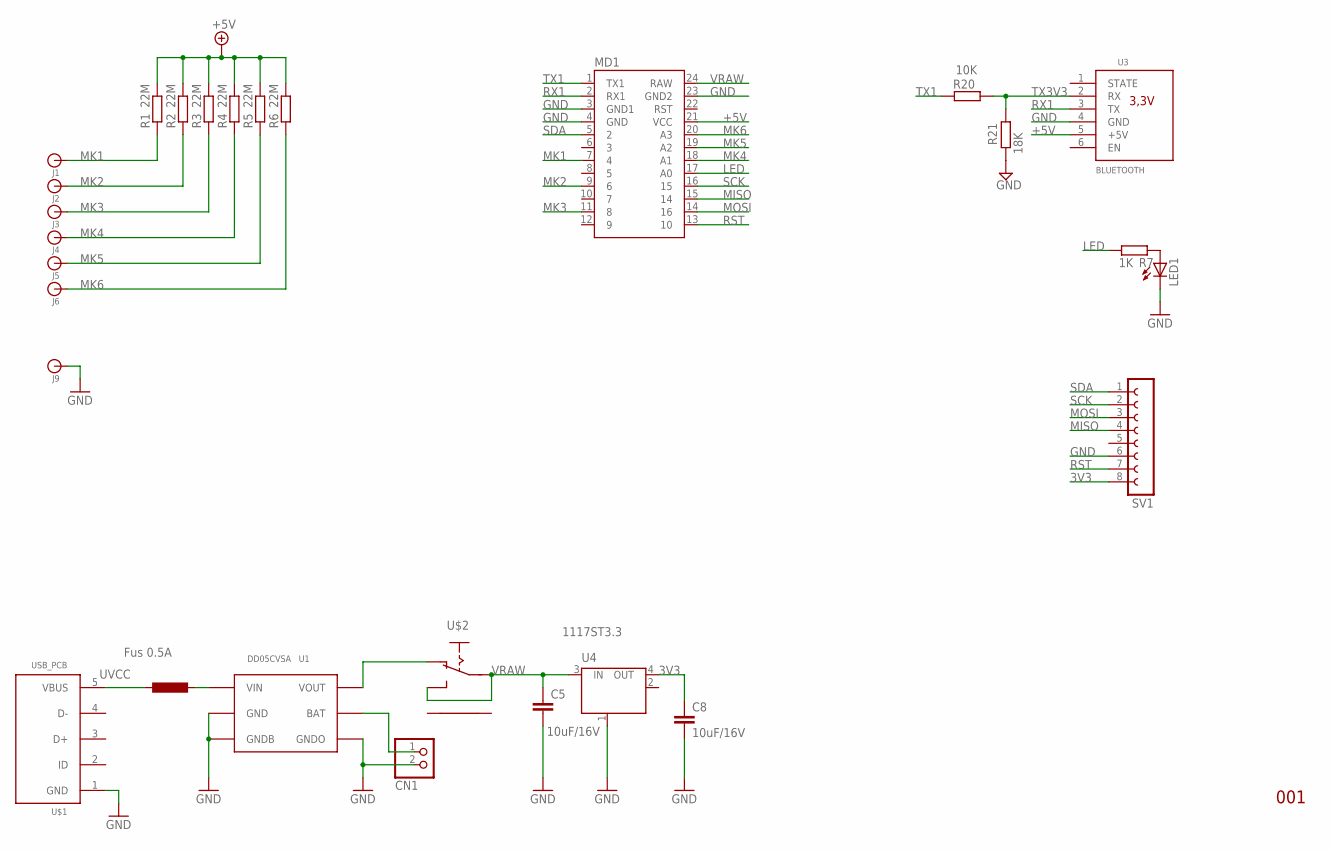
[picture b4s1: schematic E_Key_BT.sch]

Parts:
C5, C8: 10uF/16V; C1206
CN1: JST_2PIN-THM-RA; JST-PH-2-THM-RA
F1: Fus 0.5A; R1206
J1, J2, J3, J4, J5, J6, J9: Hole; BANANA_CONN
LED1: LED3MM
MD1: PRO_MICRO
R1, R2, R3, R4, R5, R6: 22M; R0603
R7: 1K; R0603
R20: 10K; R0603
R21: 18K; R0603
SV1: FE08-1; FE08
U1: DD05CVSA
U3: BLUETOOTH; BLUETOOTH_MODULE
U4: 1117ST3.3; SOT223
U$1: USB_PCB
U$2: ESCORNA_SK12F14D; ESCORNA_SK-12D07

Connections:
3V3: C8.1, SV1.8, U4.4 (OUT)
+5V: MD1.21 (VCC), R1.2, R2.2, R3.2, R4.2, R5.2, R6.2, U3.5 (+5V)
GND: C5.2, C8.2, CN1.2 (1), J9.P$1, LED1.K (C), MD1.3 (GND1), MD1.4 (GND), MD1.23 (GND2), R21.1, SV1.6, U1.P$2 (GND), U1.P$4 (GNDB), U1.P$5 (GNDO), U3.4 (GND), U4.1 (GND/ADJ), U$1.1 (GND)
LED: MD1.17 (A0), R7.2
MISO: MD1.15 (14), SV1.4
MK1: J1.P$1, MD1.7 (4), R1.1
MK2: J2.P$1, MD1.9 (6), R2.1
MK3: J3.P$1, MD1.11 (8), R3.1
MK4: J4.P$1, MD1.18 (A1), R4.1
MK5: J5.P$1, MD1.19 (A2), R5.1
MK6: J6.P$1, MD1.20 (A3), R6.1
MOSI: MD1.14 (16), SV1.3
unnamed: U1.P$6 (VOUT), U$2.P$2 (O)
unnamed: LED1.A, R7.1
unnamed: F1.1, U1.P$1 (VIN)
unnamed: CN1.1 (2), U1.P$3 (BAT)
RST: MD1.13 (10), SV1.7
RX1: MD1.2 (RX1), U3.3 (TX)
SCK: MD1.16 (15), SV1.2
SDA: MD1.5 (2), SV1.1
TX1: MD1.1 (TX1), R20.1
TX3V3: R20.2, R21.2, U3.2 (RX)
UVCC: F1.2, U$1.5 (VBUS)
VRAW: C5.1, MD1.24 (RAW), U4.3 (IN), U$2.P$1, U$2.P$3 (S)

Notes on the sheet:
001

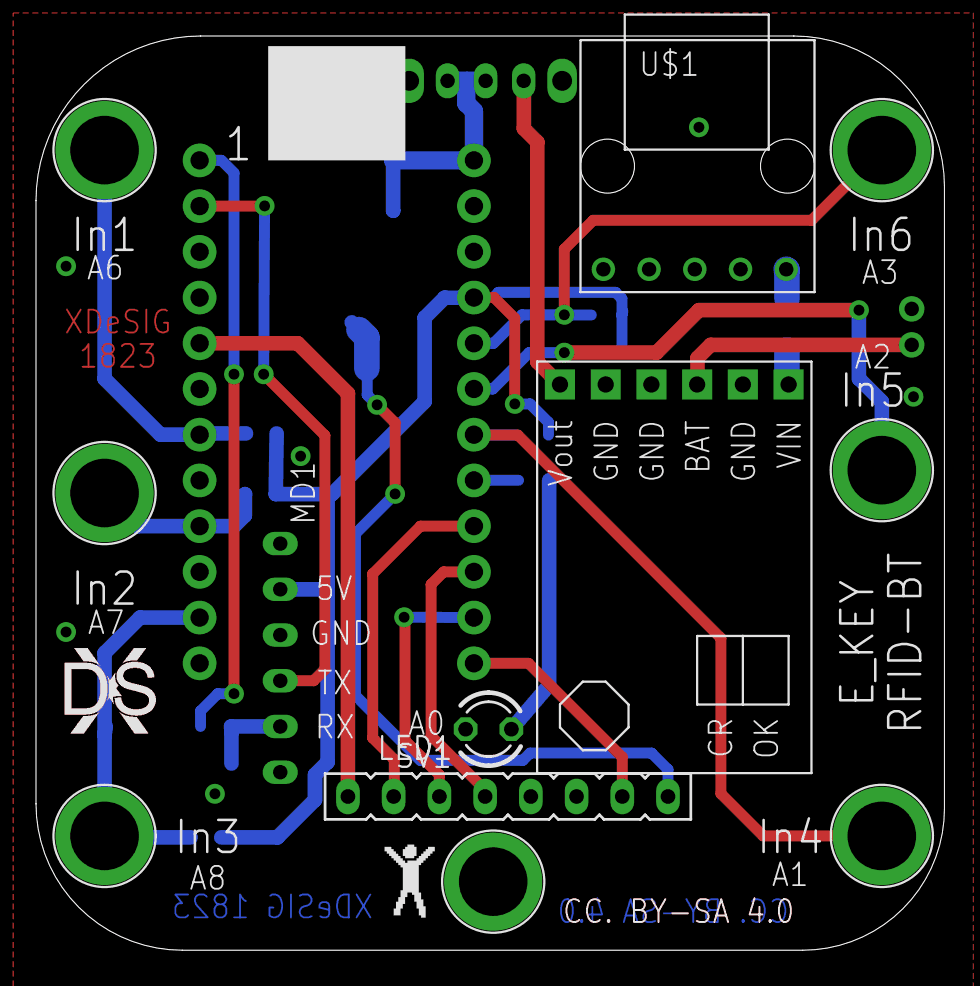
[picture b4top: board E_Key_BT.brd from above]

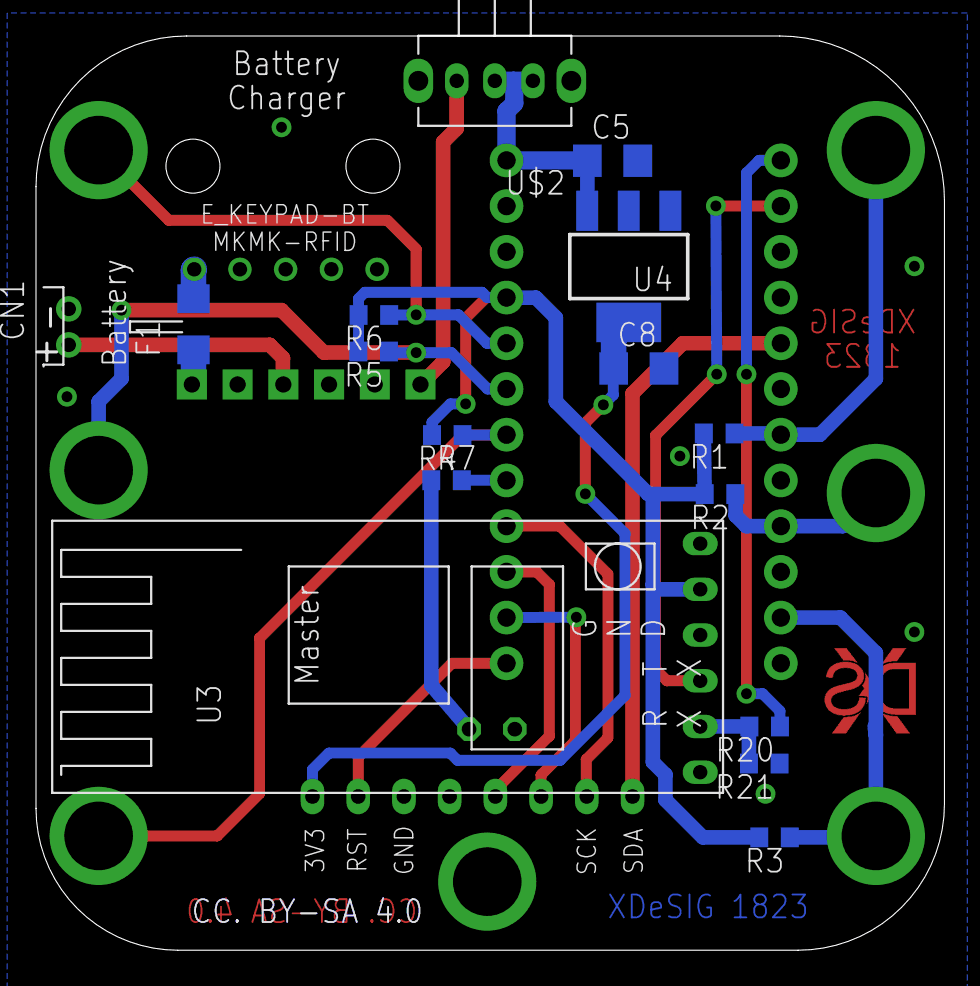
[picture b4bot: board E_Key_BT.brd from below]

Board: 2 copper layers, 50.5 x 50.8 mm, 31 parts (16 on the bottom side), 24 nets.

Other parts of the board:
U$3: XDESIG_CU
U$4: BODY
U$5: XDESIG

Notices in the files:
EscornaCPU/2.x/2.40/Escorna_CPU_2_40Amt.brd:
CERN Open Hardware Licence W V2.0
CERN-OHL-W V2.0
CERN Open Hardware Licence 2.0
parts and their libraries:
SparkFun-Aesthetics: Licensing: CC v3.0 Share-Alike You are welcome to use this library for commercial purposes.
Arduino-rcl: Copyright (c) 2016-2017 Arduino LLC.  All right reserved.
